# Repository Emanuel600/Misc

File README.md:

# Misc
miscellaneous repo

Circ_Lab: electrical circuits

DSP: Digital Signal Processing

Eletronica de Potencia: Scripts for power electronics, mostly for dimensioning circuits

Simul_Controle: Simulating control systems, '_Controle 1_' is classic control theory and the rest is modern

FizzBuzz: Programming Exercise

Multi_Thread: Testing out multithreading in C, WIP and not very serious

Sinais: Signal and Systems (LTI)

Termo: Thermodynamics (I think) - Mostly small tests for the classes

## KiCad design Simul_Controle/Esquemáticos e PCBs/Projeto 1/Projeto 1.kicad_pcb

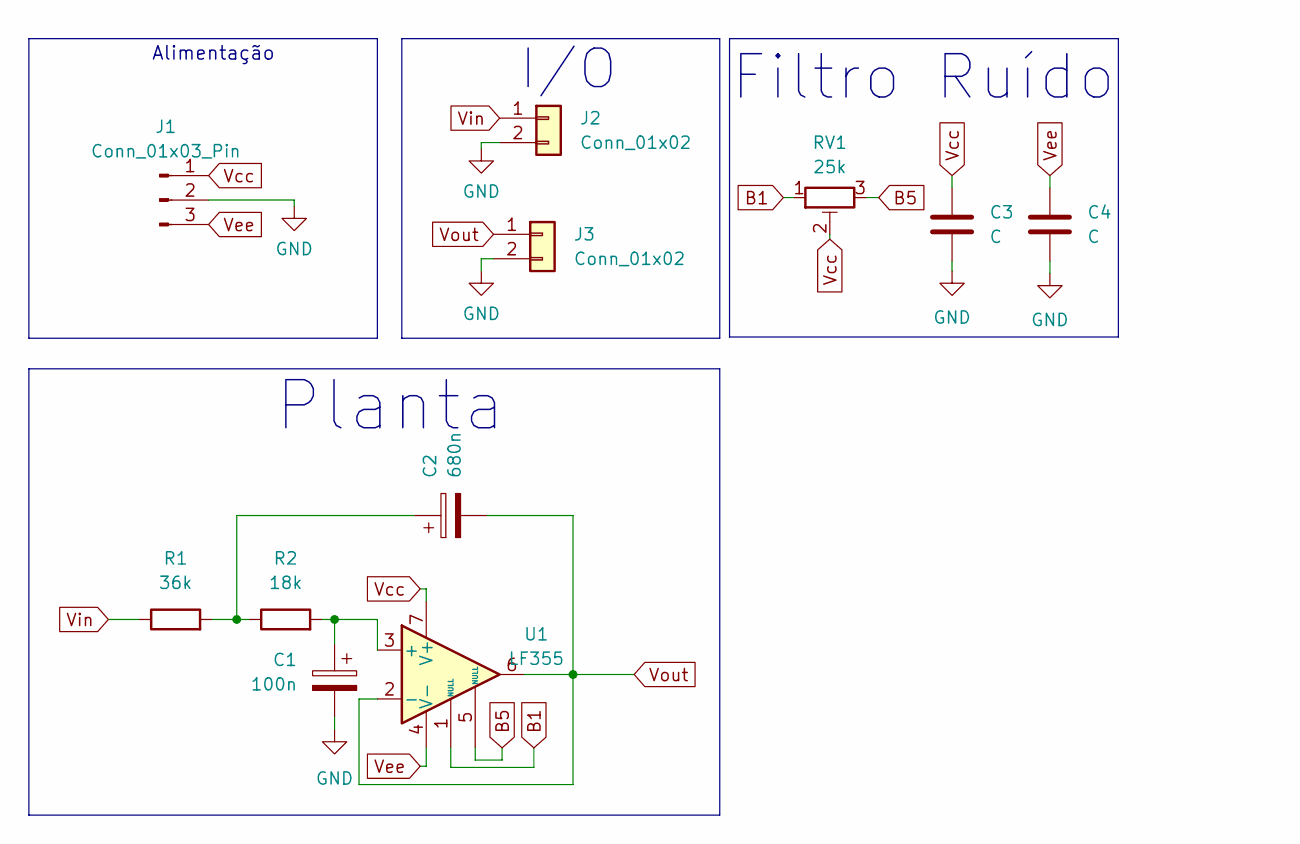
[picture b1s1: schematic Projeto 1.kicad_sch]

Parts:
C1: 100n; C_Disc_D4.7mm_W2.5mm_P5.00mm
C2: 680n; C_Disc_D7.5mm_W2.5mm_P5.00mm
C3, C4: C; C_Disc_D4.7mm_W2.5mm_P5.00mm
J1: Conn_01x03_Pin; Banana_Jack_3Pin
J2, J3: Conn_01x02; JWT_A3963_1x02_P3.96mm_Vertical
R1: 36k; R_Axial_DIN0411_L9.9mm_D3.6mm_P25.40mm_Horizontal
R2: 18k; R_Axial_DIN0411_L9.9mm_D3.6mm_P25.40mm_Horizontal
RV1: 25k; Potentiometer_Vishay_T73XW_Horizontal
U1: LF355; DIP-8_W7.62mm_LongPads

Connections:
B1: RV1.1, U1.1 (NULL)
B5: RV1.3, U1.5 (NULL)
GND: C1.2, C3.2, C4.2, J1.2, J2.2, J3.2
unnamed: C2.1, R1.2, R2.1
unnamed: C1.1, R2.2, U1.3 (+)
Vcc: C3.1, J1.1, RV1.2, U1.7 (V+)
Vee: C4.1, J1.3, U1.4 (V-)
Vin: J2.1, R1.1
Vout: C2.2, J3.1, U1.2 (-), U1.6

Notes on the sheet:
Alimentação
I/O
Planta
Filtro Ruído

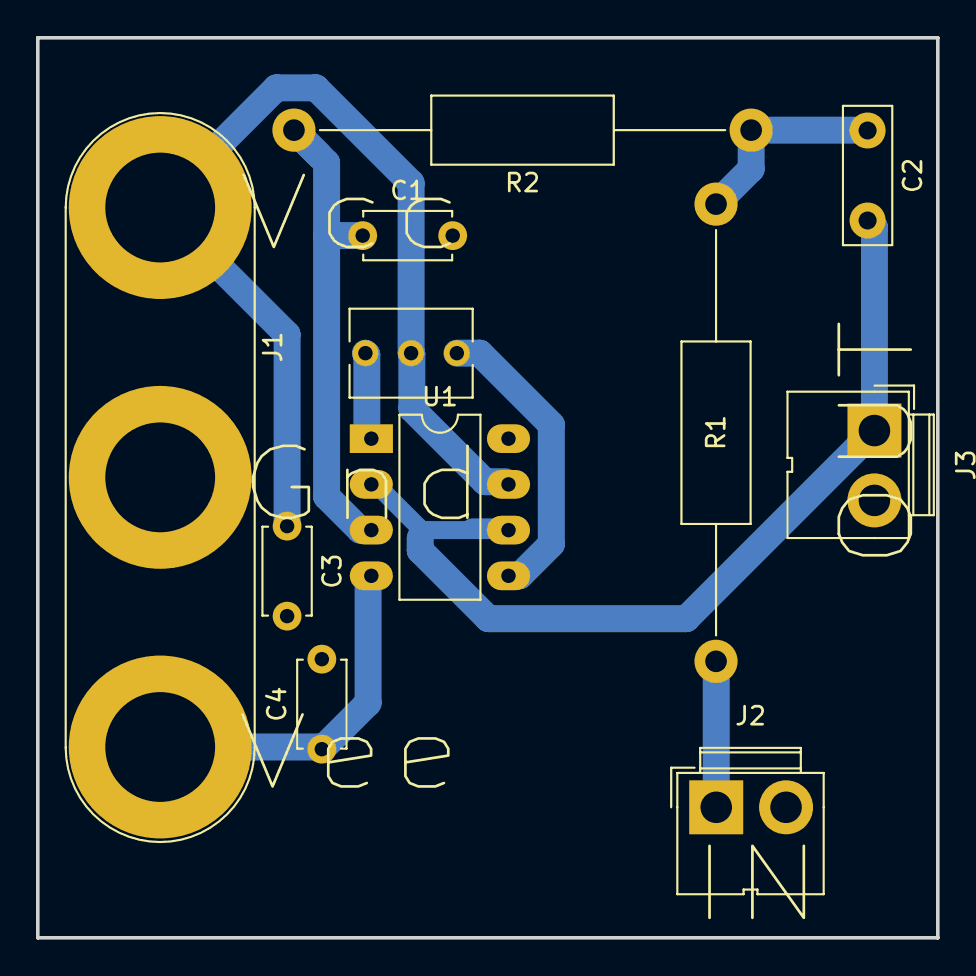
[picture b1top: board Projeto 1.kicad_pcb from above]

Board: 2 copper layers, 50.0 x 50.0 mm, 11 parts (0 on the bottom side), 9 nets.

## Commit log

2022-09-21 Rename circ3_lab3(RC) to lab03(RC).sce
2022-10-12 Erro de Sinal Concertado
    Havia um erro no sistema de equações, em que 'V<sub>f</sub>' foi inserido como positivo quando era negativo
2022-10-31 ! UNTESTED !
    CÓDIGO NÃO FOI TESTADO
    corrigido erro de offset ao adicionar escala na série de Fourier
2022-11-06 Create four_circ_param
2023-11-02 Rename Transfer.py to Redes/Transfer.py
2023-11-02 Rename Transfer.py to Transfer.py
2023-11-29 Temp
2023-11-29 Fixed Local Repo
2023-12-16 This is Not Working
2023-12-16 It works now
2023-12-16 Removed HUGE commented block from failed attempt at being clever
2023-12-17 Changed folders for better organizing
2023-12-17 All Fixed And Ready
2023-12-17 Better readability/documentation
2023-12-17 Optimized
2023-12-17 Better UX
2024-02-11 Testing Some Stuff
2024-02-11 Renamed a folder for better readability
2024-03-03 DSP Added, already has some stuff (~3 hours of work)
2024-03-04 Added timme shift and convolution, as well as QoL improvements on plots
2024-03-11 Added support for diferent 'n' vectors
2024-03-11 Added description for the folders
2024-03-19 Added Simul_Controle
2024-03-19 I think it worked
2024-03-19 Re-moved Monty Hall sym to its previous folder
2024-03-20 Finished merge with other repo and repositioned a comment to be more sensible
2024-03-20 Fixed error from deleting a comment with CTRL+Backspace
2024-03-20 I'm not sure what changed, but git is telling me something did
2024-03-24 Fixed xcos simulation issues
2024-03-25 Added small function to equalize 'n'
2024-03-25 QoL improvements on operations
2024-03-25 Added Fourier (WIP)
2024-03-25 Fourier still not working, starting on another branch
2024-03-25 Added guard on Lourier loop
2024-03-25 Better plotting for Fourier
2024-03-25 Changed Fourier to be matrix multiplication
2024-03-25 Changed plot settings
2024-03-25 Tried to fix error on Fourier transform
2024-03-25 Changing Fourier again
2024-03-26 Trying to add IDFT
2024-03-29 Improvements to IDTFT
2024-03-29 Improvements to Fourier
2024-03-29 Completed DTFT And IDTFT
2024-03-30 Small fix-up to Fourier
2024-03-30 Added obs to inv_four
2024-03-31 Added options for plotting and DTFT
2024-04-02 Added LPF and optimized Fourier plotting and QoL improvements
2024-04-02 Better filters (lpf -> filter)
2024-04-03 Better Plots
2024-04-25 There's a reason these weren't tracked
2024-04-26 Questão 3 corrigida
2024-04-26 Q1 Corrigida
2024-04-26 Q4 corrigida
2024-04-27 Q4 completa
2024-05-30 P1 Refeita do zero
2024-05-30 P1 - Recorrigida
2024-07-06 Prova Corrigida (Denovo)
2024-07-11 Testing out threading
2024-08-20 Still Finishing
2024-08-21 Added Various Windows to FFT
2024-08-25 Added some QL stuff
2024-08-29 Terminando Trabelho de Fase
2024-09-01 Finished Filter Design, just re-check later
2024-09-01 Added relevant files
2024-09-02 Finalisando Filtros
2024-09-03 Terminando Filtros, falta revisar
2024-09-04 Finished All DSP work
2024-10-08 When did I change this? Might have been just jupyter being weird
2024-10-08 Gerador de tons é o principal, o resto é update de atividades anteriores. Simplesmente degra tons DTMF de acordo com a tabela
2024-10-20 Adicionando média móvel e grid para o Plot_FFT
2024-10-20 Added files for power electronics
2024-10-20 Added old Classic Controll sims
2024-10-20 New files for digital control sims, osci_read is to practice reading osciloscope data
2024-10-22 Significant improvement to doublesp()s execution time; dont know why Gerador_Tons.ipynb was deleted so it got restored; Finished the brunt of the work for Processamento_Audio.ipynb, almost ready to b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
2024-10-22 DSP was not updated on previous push, significant improvement on doublesp execution time
2024-10-23 Finished Processamento_Audio and added grids to DSP.plot for convenience
2024-10-25 Adding some code from thumb drive"
2024-10-25 Added SEPIC script, not tested yet
2024-10-25 Fixed SEPIC.sce and tested it, results somewhat inconclusive, will check with professor later or compare with an example from the book
2024-10-25 Fixed small error on Cuk converter that stemmed from a misinterpretation on the books equations
2024-10-26 Added separate current variations for each inductor on SEPIC.sce, dont know whether Ill do the same for the capacitors
2024-10-26 Added specific real models to LTSpice simulation for the first project
2024-10-26 Standardized Analogico.ipynb formatting
2024-10-26 Added schematics for control 2, including pcb file for kicad
2024-10-27 Made some changes to configs and trail thickness
2024-10-27 Small alterations, I think
2024-10-27 Added teardrops, will see if theyre kept
2024-10-27 Fixed errors on board inspection and brought RV1 closer to opamp in hopes of minimizing noise, probably wont help much
2024-10-29 Pre last resort filter, still has an annoying high pitched noise in, but that should be gone with the 2 kHz filter that will be applied later
2024-10-29 Added last resort 2 kHz filter and the actual file this commit was supposed to include, works great after normalization prima faci, will check again tomorrow. For now, all thats left is to add markdo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
2024-10-29 Forgot to add the filter coefficientes csv, soon finishing the markdown cells
2024-10-29 Filter coefficients have been adjusted for csv and tested on ocenaudio
2024-10-29 Finished markdown
2024-10-29 I think this is finished, but I should probably check with the professor
2024-10-29 Small Update on dB scale for FFT
2024-10-31 Fixed typo on LF356 (previously 336) and added simulation for LF351, which was the closest available IC
2024-10-31 Renamed Analogico to Projeto 1
2024-10-31 Added z transform and discrete step response with z-plane root locus of the plant
2024-10-31 Fixed errors on calculating amostrating period and added a convenience file to define some commonly used functions that will be filled out in the future
2024-11-02 Separated Projeto 1 into 2 files, will probably break into multiple more later. Added the recursive equation for Gz wich may serve as a prototype for similar functions in controle.py for use in later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
2024-11-02 Trying to add a controller, will be trying a different method for calculating the angle for z1
2024-11-03 Tried new method on example, worked perfectly. Moving on to real problem
2024-11-03 Changed for the real values, but still does not work
2024-11-03 Compensator worked, but I need a pole in z=1 (beta=-1)
2024-11-03 Nothings working
2024-11-06 Adicionado conversor flyback
2024-11-07 Best function I could get, has little fundamentation
2024-11-07 Added an integrator to fix ss error, trying to fix gain issues now
2024-11-07 Fixed integrator gain and minimized its inpact on the LR
2024-11-08 Renamed files for better readability and consistency
2024-11-15 Added a few files for control and eletronics, controle is moving on to modeling the real plant and calculating controller parameters for it
2024-11-15 Controller design seems almost perfect now, will revise later
2024-11-16 Finished controller design. Added recursive equations for both the microcontroler and the plant, will think of a way to unite both later
2024-11-19 Added Recursive Equations Simulation, still needs some fixing
2024-11-19 Fixed it, as usal: it was a simple error that I kept overlooking
2024-11-19 Fixed it
2024-11-19 Better syntax and formatting, also made it easier to convert to uC C++ code later
2024-11-19 Minor formatting stuff and removing as many Complex Casting warnings as possible. These warnings stem from the denominator of the Transfer Functions beign converted into a b array, I do not know why,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
2024-11-22 Comparando vários conversores com os mesmos parâmetros para verificar os scripts e ver se há alguma diferença em seu funcionamento
2024-11-22 Added Comparison between Full Bridge and Half-Bridge, also clarified that PP converter has two primary coils on graphs
2024-11-22 Added C sym, made the recursive implementation of the controller in C and added the plant for simulation, the plant will be removed later when the code gets adapted for microcontrollers - will also r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
2024-11-23 Added Real Implementatios of filters, notch filter needs some work but the rest are fine
2024-11-23 Changed recursive equation simulation to a real time simulation, this should be directly and immediatly implementable on MicroControllers
2024-11-24 Changed location of pole according to specifications given. Will tag this and previous versions just to be safe since I dont know what Ill need later
2024-11-28 Updated csv, dont know how I missed that. Added current project to power electronics and finished a DSP project
2024-11-29 Testing on Buck-Boost files and slightly advanced the project for the DC-DC Converter
2025-01-30 Added worksheet on image correction/modification
2025-02-04 Started work on State Space Control, still on beggining stages
2025-02-15 Added State Space controller and observer, also compared observer results with simulation on LTSpice
2025-02-15 Slight improvements to quality of the plots, also added an indirect observer and a dubious estimation of the control action
2025-02-15 Removed duplicate of matrix A, likely a copy-paste error
2025-02-15 Implementing observer by recursive equations (WIP) and parts of plant+controller (finished)
2025-02-15 Finished implementing observer, moving on to implementing a different, hopefully better observer
2025-02-15 Finished designing controller and observer, indirect implementation of observer failed, likely due to an error on the estimation of the derivative of Vc
2025-02-16 Dont remember what changed
2025-02-17 Added Final project for DSP, currently can separate an image into single words, need to separate into letters
2025-02-20 Some changes to exploratory notebook, tagging current version of Control to try a different solution
2025-02-20 Made C=[1 0] for better controlability
2025-02-23 Finished Control Project
2025-02-24 Added labels and a few py files to start training the model
2025-02-25 Finished some testing and redied the notebook for presentation
2025-03-30 Added a calculator and generic tester class, does not support negative numbers
2025-04-03 Almost finished documentation and added a debug macro for convenience
2025-05-01 Fixed memory leak and minor test change for #13 - The reason test #13 fails is due to a rounding error when converting the string to a double
